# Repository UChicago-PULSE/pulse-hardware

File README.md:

# pulse-hardware
This is the central repository for documents related to PULSE-A hardware development. Each subteam has a folder containing documentation for their specific hardware. 

# Subteam Folders
Subteams are in charge of managing their respective folders in accordance with our teamwide git SOP. Please see the Git SOP document on Notion for more details.

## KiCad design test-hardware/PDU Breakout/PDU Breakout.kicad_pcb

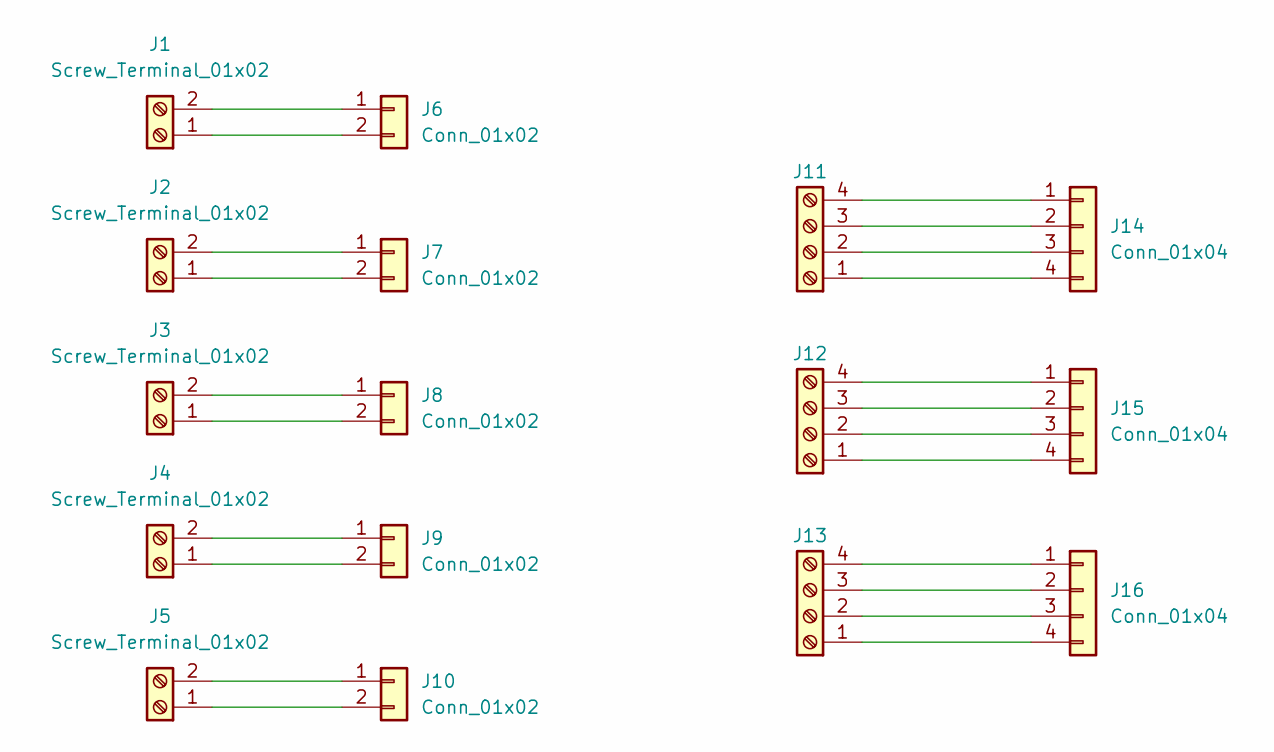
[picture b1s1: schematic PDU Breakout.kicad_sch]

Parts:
J1, J2, J3, J4, J5: Screw_Terminal_01x02; TerminalBlock_Phoenix_PT-1,5-2-3.5-H_1x02_P3.50mm_Horizontal
J6, J7, J8, J9, J10: Conn_01x02; Molex_Pico-Lock_205338-0002_1x02-1MP_P2.00mm_Horizontal
J11, J12, J13: Screw_Terminal_01x04; TerminalBlock_Phoenix_PT-1,5-4-3.5-H_1x04_P3.50mm_Horizontal
J14, J15, J16: Conn_01x04; Molex_Pico-Lock_205338-0004_1x04-1MP_P2.00mm_Horizontal

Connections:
unnamed: J1.1, J6.2
unnamed: J1.2, J6.1
unnamed: J2.1, J7.2
unnamed: J2.2, J7.1
unnamed: J3.1, J8.2
unnamed: J3.2, J8.1
unnamed: J4.1, J9.2
unnamed: J4.2, J9.1
unnamed: J5.2, J10.1
unnamed: J5.1, J10.2
unnamed: J11.1, J14.4
unnamed: J11.2, J14.3
unnamed: J11.3, J14.2
unnamed: J11.4, J14.1
unnamed: J12.1, J15.4
unnamed: J12.2, J15.3
unnamed: J12.3, J15.2
unnamed: J12.4, J15.1
unnamed: J13.1, J16.4
unnamed: J13.2, J16.3
unnamed: J13.3, J16.2
unnamed: J13.4, J16.1

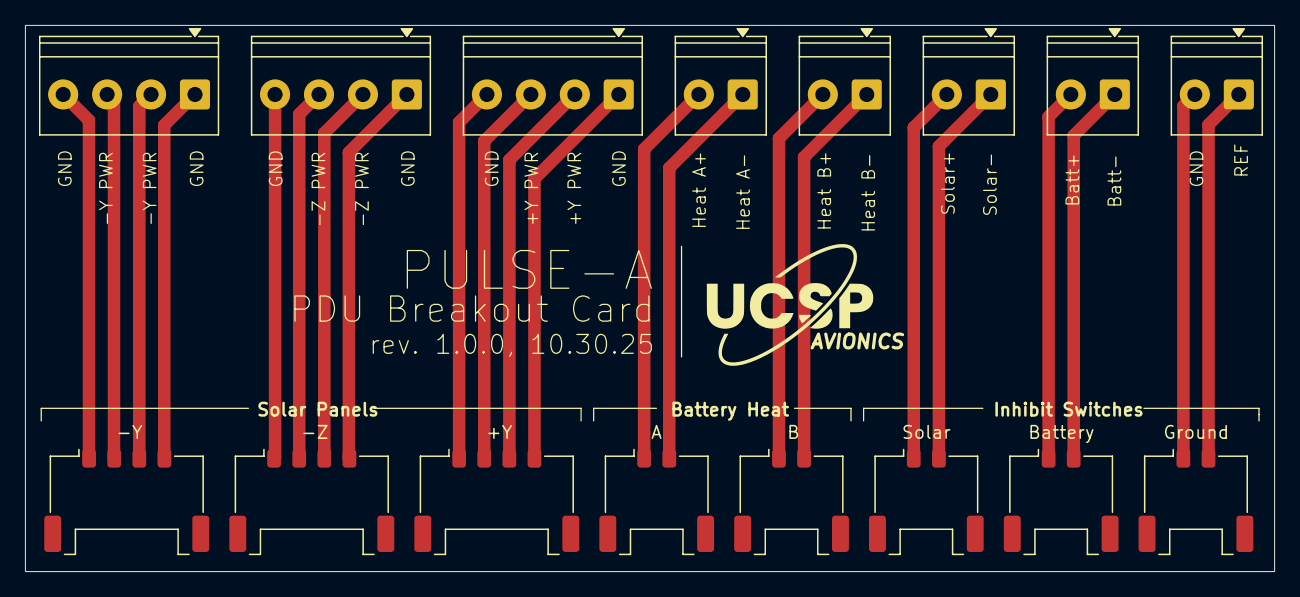
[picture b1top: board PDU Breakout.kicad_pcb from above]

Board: 2 copper layers, 99.5 x 43.5 mm, 16 parts (0 on the bottom side), 22 nets.

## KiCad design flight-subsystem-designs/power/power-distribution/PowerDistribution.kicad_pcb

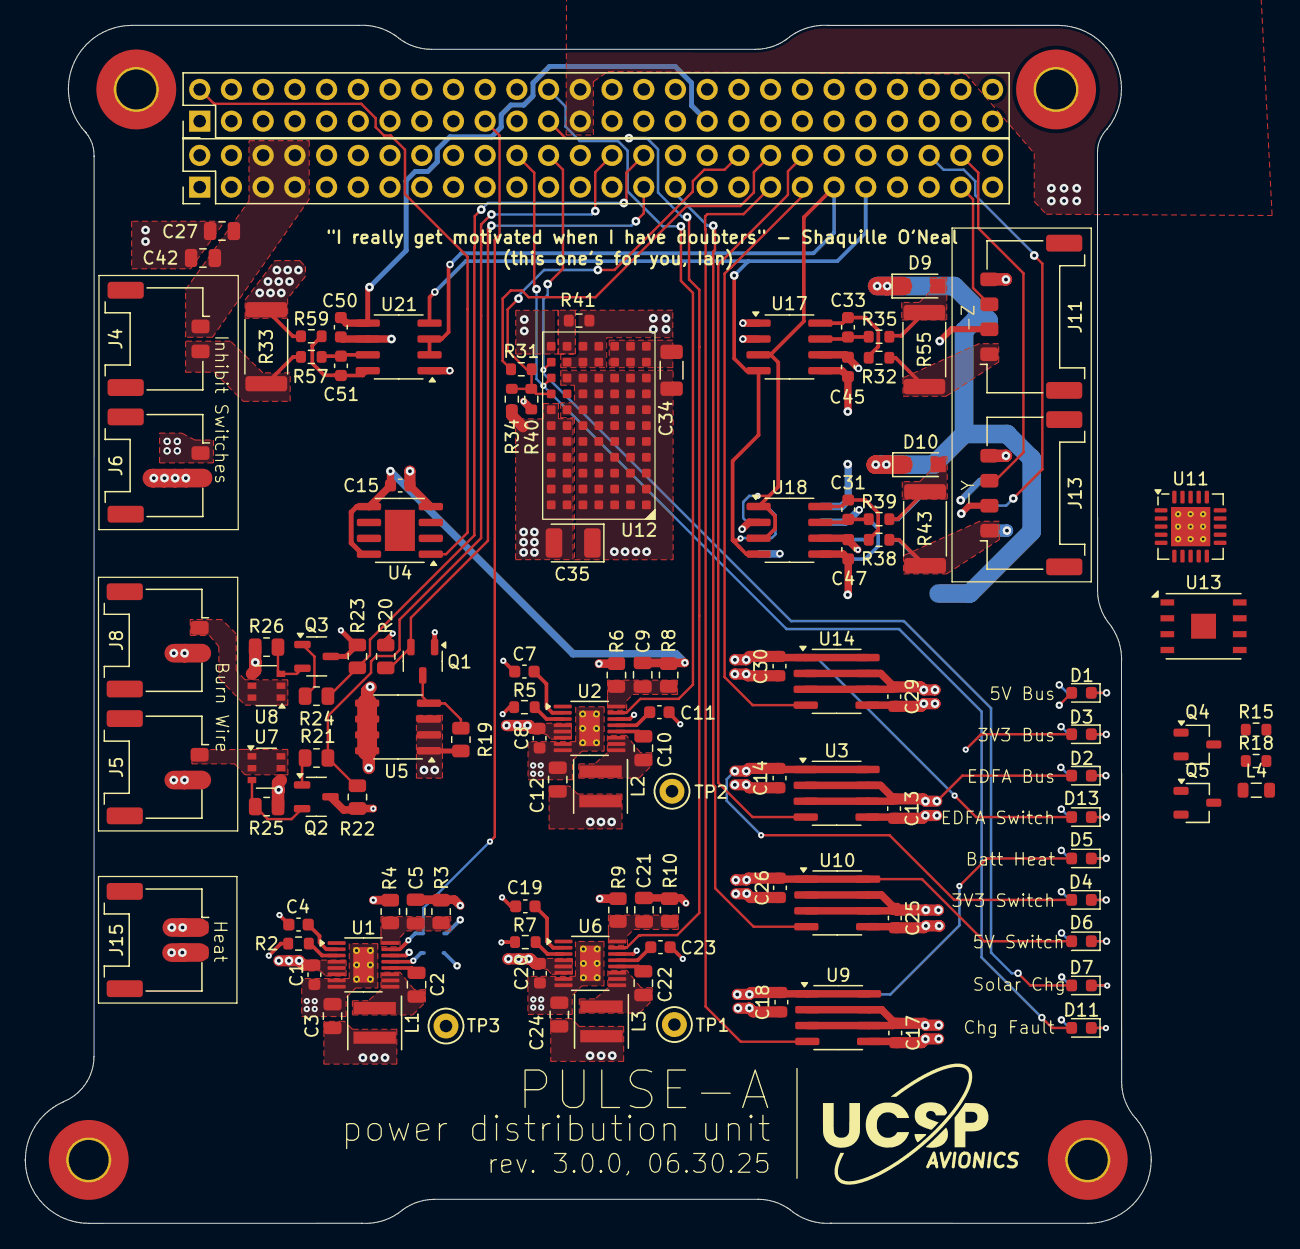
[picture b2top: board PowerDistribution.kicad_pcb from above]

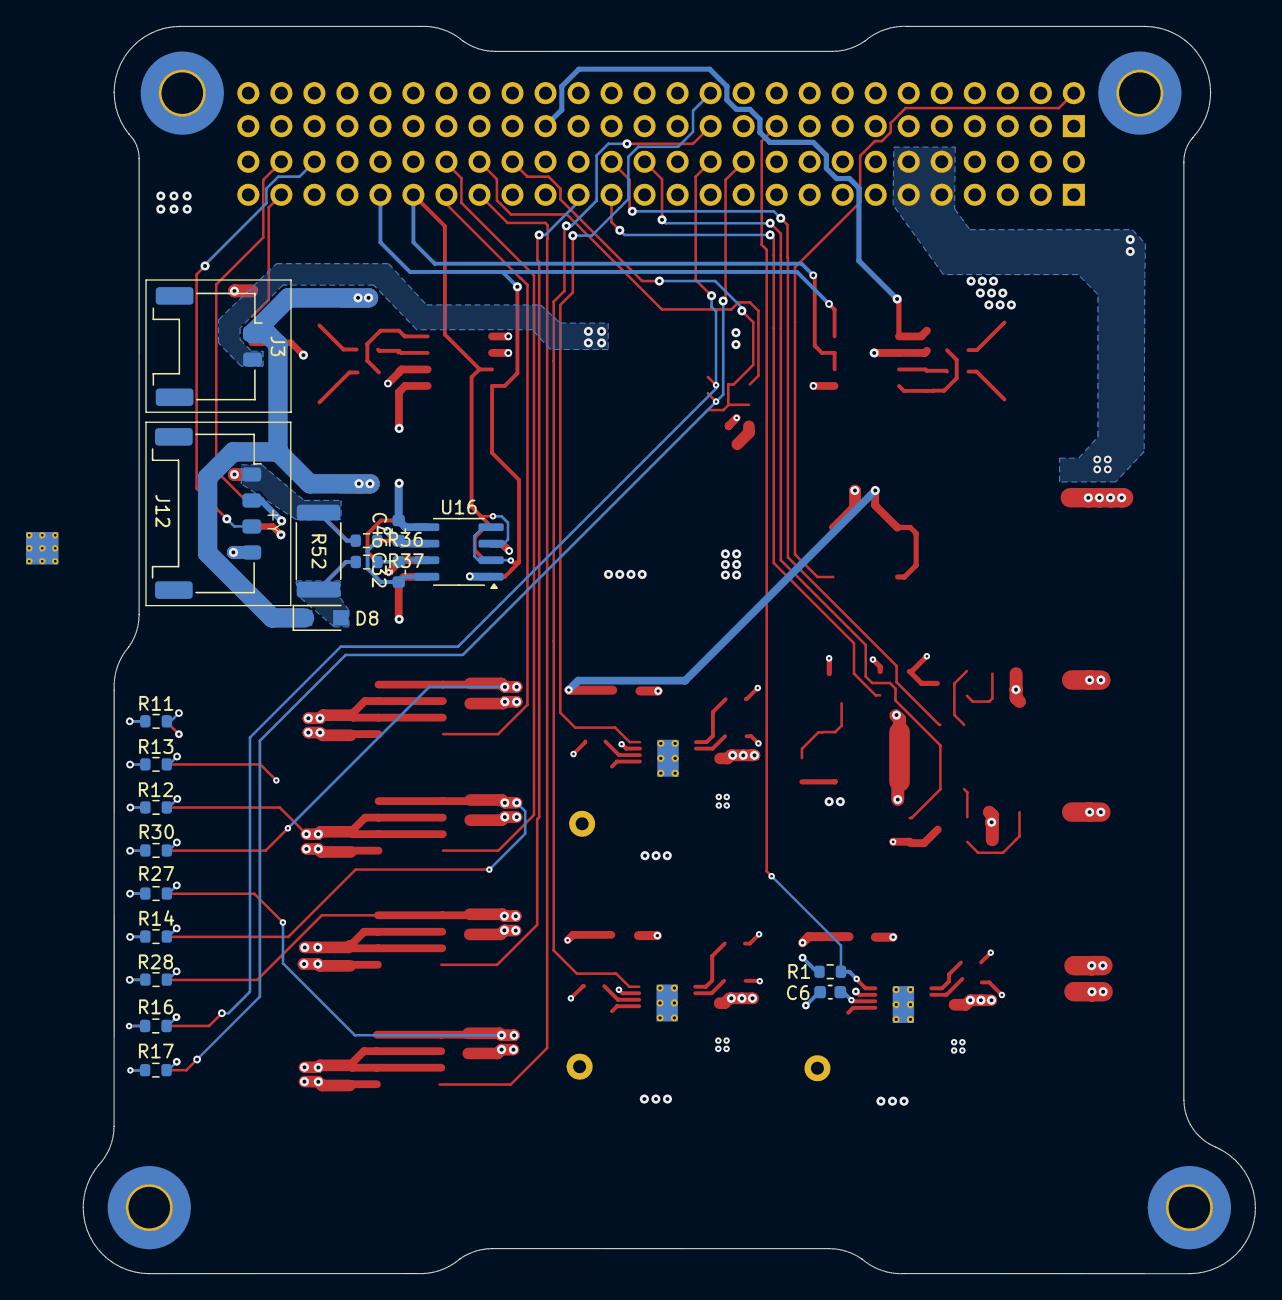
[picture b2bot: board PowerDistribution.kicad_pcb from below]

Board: 4 copper layers, 90.2 x 96.0 mm, 141 parts (20 on the bottom side), 91 nets.

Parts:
C1, C8, C20: 4.7uF; C_0603_1608Metric
C2, C10, C22, C27: 0.1uF; C_0805_2012Metric
C3, C12, C24: 68uF; C_0805_2012Metric
C4, C7, C19: 10nF; C_0603_1608Metric
C5, C21: 10pF; C_0805_2012Metric
C6, C11, C14, C18, C23, C26, C30, C31, C32, C33, C51: 1uF; C_0603_1608Metric
C9: 4.7pF; C_0805_2012Metric
C13, C15, C17, C25, C29: 0.1uF; C_0603_1608Metric
C34: 4.7uF; C_1206_3216Metric
C35: 4.7uF; CP_EIA-3528-12_Kemet-T
C42: 22uF; C_0805_2012Metric
C45, C46, C47, C50: 0.1UF; C_0603_1608Metric
D1, D2, D3, D7, D11: 150060VS75000; LED_0603_1608Metric
D4, D5, D6, D13: 150060AS75000; LED_0603_1608Metric
D8, D9, D10: PMEG10020ELRX; Nexperia_CFP3_SOD-123W
H1, H2, H3, H4: MountingHole; MountingHole_3.2mm_M3_Pad_TopBottom
J1, J2: Conn_02x26_Odd_Even; PinHeader_2x26_P2.54mm_Vertical
J3, J4, J5, J6, J8, J15: Conn_01x02; Molex_Pico-Lock_205338-0002_1x02-1MP_P2.00mm_Horizontal
J11, J12, J13: Conn_01x04; Molex_Pico-Lock_205338-0004_1x04-1MP_P2.00mm_Horizontal
L1, L3: 10uH; L_Coilcraft_XxL4040
L2: 8.2uH; L_Coilcraft_XxL4040
L4: AIMC-0805-2N2S-T; L_0805_2012Metric
Q1: BC848ALT1G; SOT-23-3
Q2, Q3: IRLML2803PBFCT; SOT-23-3
Q4, Q5: NMOS; TSOT-23
R1: 100k; R_0603_1608Metric
R2, R5, R7: 110k; R_0603_1608Metric
R3, R8, R10: 1M; R_0805_2012Metric
R4, R9: 243k; R_0805_2012Metric
R6: 412k; R_0805_2012Metric
R11, R12, R14, R16, R17, R27, R28: 150; R_0603_1608Metric
R13, R30: 65; R_0603_1608Metric
R15, R18: 1M; R_0603_1608Metric
R19, R20, R22, R23: 10k; R_0805_2012Metric
R21, R24: 4.7k; R_0805_2012Metric
R25, R26: 100k; R_0805_2012Metric
R31, R34: 549k; R_0603_1608Metric
R32, R35, R36, R37, R38, R39, R57, R59: 10; R_0603_1608Metric
R33, R43, R52, R55: 2m; R_2512_6332Metric
R40: 459k; R_0603_1608Metric
R41: 0; R_0603_1608Metric
TP1, TP2, TP3: TestPoint_Keystone_5000-5004_Miniature
U1, U2, U6: LT8610; MSOP-16-1EP_3x4.039mm_P0.5mm_EP1.651x2.845mm_ThermalVias
U3, U5, U9, U10, U14: SOIC-8_3.9x4.9mm_P1.27mm
U4: SOIC-8-1EP_3.9x4.9mm_P1.27mm_EP2.41x3.3mm
U7, U8: TSOP-6_1.65x3.05mm_P0.95mm
U11: Texas_RGW0020A_VQFN-20-1EP_5x5mm_P0.65mm_EP3.15x3.15mm_Ther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
U12: LTM8062AIV-PBF; LGA-77
U13: DFN-8-1EP_6x5mm_P1.27mm_EP2x2mm
U16, U17, U18, U21: INA219AxD; SOIC-8_3.9x4.9mm_P1.27mm

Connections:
3V3: C9.2, C12.2, C15.2, C29.1, D3.2 (A), J2.27, J2.28, J11.2, J12.2, J13.2, L2.2, R8.2, TP2.1, U2.14 (BIAS), U4.5 (SHUTDOWN), U4.8 (V_IN), U13.8 (VDD), U14.2 (V_IN1), U14.3 (V_INS), U14.6 (V_IN3), U14.7 (V_IN2)
3V3_S: C30.1, C45.2, C46.2, C47.2, C50.2, D13.2 (A), J1.34, J2.33, U14.1 (V_OUT1), U14.8 (V_OUT2), U16.5 (VS), U17.5 (VS), U18.5 (VS), U21.5 (VS)
3V3_STAT: J2.24, U2.15 (PG)
3V3_S_EN: J1.39, U14.4 (EN)
5V: C17.1, C21.2, C24.2, C25.1, D1.2 (A), J2.25, J2.26, L3.2, R10.2, TP1.1, U6.14 (BIAS), U9.2 (V_IN1), U9.3 (V_INS), U9.6 (V_IN3), U9.7 (V_IN2), U10.2 (V_IN1), U10.3 (V_INS), U10.6 (V_IN3), U10.7 (V_IN2)
5V_S: C26.1, D6.2 (A), J1.45, J1.46, U10.1 (V_OUT1), U10.8 (V_OUT2)
5V_STAT: J2.23, U6.15 (PG)
5V_S_EN: J1.31, U10.4 (EN)
/ADJ: J1.36, R31.2, R34.1, R40.2, U12.H7 (ADJ)
/BATT_CS: J4.2, R33.1, R57.1
/BATT_THERM_R: J1.38, R31.1
/CHARGE_VIN: C34.2, U12.K1 (VIN), U12.K2 (VIN), U12.K3 (VIN), U12.L1 (VIN), U12.L2 (VIN), U12.L3 (VIN)
/CHRG: D7.2 (A), J1.24, U12.K7 (*CHRG)
/CS_SOL1_VIN+: C33.2, R32.1, U17.8 (IN+)
/CS_SOL1_VIN-: C33.1, R35.1, U17.7 (IN-)
/CS_SOL2_VIN+: C32.2, R36.1, U16.8 (IN+)
/CS_SOL2_VIN-: C32.1, R37.1, U16.7 (IN-)
/CS_SOL3_VIN+: C31.2, R38.1, U18.8 (IN+)
/CS_SOL3_VIN-: C31.1, R39.1, U18.7 (IN-)
/FAULT: D11.2 (A), J1.22, U12.J7 (*FAULT)
/FB_1: C5.1, R3.1, R4.2, U1.16 (FB)
/FB_2: C9.1, R6.2, R8.1, U2.16 (FB)
/FB_3: C21.1, R9.2, R10.1, U6.16 (FB)
/PDU_TEMP: J2.2, U4.1 (V_OUT)
/RBF_SW: Q4.2 (G), R15.2
/SOLAR_IN_+Y: J12.1, R36.2, R52.2
/SOLAR_IN_-Y: J13.1, R38.2, R43.2
/SOLAR_IN_-Z: J11.1, R32.2, R55.2
/SOLAR_PRE_MPPT: J3.2, R41.1, U12.K4 (VINA), U12.K5 (VINA), U12.K6 (RUN), U12.L4 (VINA), U12.L5 (VINA)
/SOLAR_TMP_+Y: J1.48, J12.3
/SOLAR_TMP_-Y: J1.50, J13.3
/SOLAR_TMP_-Z: J1.49, J11.3
/SW_1: C2.2, L1.1, U1.9 (SW), U1.10 (SW), U1.11 (SW)
/SW_2: C10.2, L2.1, U2.9 (SW), U2.10 (SW), U2.11 (SW)
/SW_3: C22.2, L3.1, U6.9 (SW), U6.10 (SW), U6.11 (SW)
/VBATT_IN: C27.2, C42.2, J1.5, J1.6, J1.7, J1.8, Q5.1 (D), R18.2
/VBATT_PRE_INH: J4.1, Q5.3 (S)
/VIN_REG: R41.2, U12.L6 (VINREG)
/b1: J5.1, U7.1 (D2), U7.2 (D3), U7.5 (D4), U7.6 (D1)
/b2: J8.1, U8.1 (D2), U8.2 (D3), U8.5 (D4), U8.6 (D1)
/sol_1_diode: D9.2 (A), R35.2, R55.1
/sol_2_diode: D8.2 (A), R37.2, R52.1
/sol_3_diode: D10.2 (A), R39.2, R43.1
BURN_FET: J1.29, Q1.2 (B), R20.1
EDFA_5V: C3.2, C5.2, C13.1, D2.2 (A), L1.2, R1.1, R3.2, TP3.1, U1.14 (BIAS), U3.2 (V_IN1), U3.3 (V_INS), U3.6 (V_IN3), U3.7 (V_IN2)
EDFA_5V_EN: J1.40, U3.4 (EN)
EDFA_5V_S: C14.1, D4.2 (A), J1.42, J1.44, U3.1 (V_OUT1), U3.8 (V_OUT2)
EDFA_5V_STAT: J2.19, R1.2, U1.15 (PG)
ENAB_BURN_1: J1.28, R21.2, R22.1
ENAB_BURN_2: J1.30, R23.1, R24.2
GND: C1.1, C3.1, C4.1, C6.2, C7.1, C8.1, C11.2, C12.1, C13.2, C14.2, C15.1, C17.2, C18.2, C19.1, C20.2, C23.2, C24.1, C25.2, C26.2, C29.2, C30.2, C34.1, C35.1, C45.1, C46.1, C47.1, C50.1, J2.29, J2.30, J2.31, J2.32, J5.2, J6.2, J8.2, J11.4, J12.4, J13.4, J15.2, L4.1, Q1.1 (E), Q2.3 (S), Q3.3 (S), R2.2, R4.1, R5.2, R6.1, R7.2, R9.1, R11.1, R12.1, R13.1, R14.1, R16.1, R17.1, R20.2, R22.2, R23.2, R27.1, R28.1, R30.1, R40.1, U1.7 (GND), U1.8 (GND), U1.17 (GND), U2.7 (GND), U2.8 (GND), U2.17 (GND), U3.5 (GND), U4.4 (GND), U6.7 (GND), U6.8 (GND), U6.17 (GND), U9.5 (GND), U10.5 (GND), U12.A1 (GND), U12.A2 (GND), U12.A3 (GND), U12.A4 (GND), U12.A5 (GND), U12.B1 (GND), U12.B2 (GND), U12.B3 (GND), U12.B4 (GND), U12.B5 (GND), U12.C1 (GND), U12.C2 (GND), U12.C3 (GND), U12.C4 (GND), U12.C5 (GND), U12.D1 (GND), U12.D2 (GND), U12.D3 (GND), U12.D4 (GND), U12.D5 (GND), U12.E1 (GND), U12.E2 (GND), U12.E3 (GND), U12.E4 (GND), U12.E5 (GND), U12.F1 (GND), U12.F2 (GND), U12.F3 (GND), U12.F4 (GND), U12.F5 (GND), U12.G1 (GND), U12.G2 (GND), U12.G3 (GND), U12.G4 (GND), U12.G5 (GND), U12.G6 (GND), U12.H1 (GND), U12.H2 (GND), U12.H3 (GND), U12.H4 (GND), U12.H5 (GND), U12.J1 (GND), U12.J2 (GND), U12.J3 (GND), U12.J4 (GND), U12.J5 (GND), U12.J6 (TMR), U12.L7 (GND), U13.4 (GND), U14.5 (GND), U16.1 (A1), U16.6 (GND), U17.1 (A1), U17.2 (A0), U17.6 (GND), U18.2 (A0), U18.6 (GND), U21.1 (A1), U21.6 (GND)
GND_REF: C27.1, C42.1, J1.9, J1.10, J1.11, J1.12, J6.1
KAPTON_EN: J1.37, U9.4 (EN)
KAPTON_PWR: C18.1, D5.2 (A), J15.1, U9.1 (V_OUT1), U9.8 (V_OUT2)
unnamed: D1.1 (K), R11.2
unnamed: D2.1 (K), R12.2
unnamed: D3.1 (K), R13.2
unnamed: D4.1 (K), R14.2
unnamed: D5.1 (K), R27.2
unnamed: D6.1 (K), R28.2
unnamed: D7.1 (K), R16.2
unnamed: D11.1 (K), R17.2
unnamed: D13.1 (K), R30.2
unnamed: Q1.3 (C), R19.2, U5.4 (G)
unnamed: Q2.2 (D), R25.1, U7.3 (G)
unnamed: Q2.1 (G), R21.1
unnamed: Q3.2 (D), R26.1, U8.3 (G)
unnamed: Q3.1 (G), R24.1
unnamed: Q4.1 (D), Q5.2 (G), R18.1
unnamed: L4.2, Q4.3 (S), R15.1
unnamed: C2.1, U1.12 (BST)
unnamed: C6.1, U1.13 (INTVcc)
unnamed: R2.1, U1.3 (RT)
unnamed: C4.2, U1.2 (TR/SS)
unnamed: C10.1, U2.12 (BST)
unnamed: C11.1, U2.13 (INTVcc)
unnamed: R5.1, U2.3 (RT)
unnamed: C7.2, U2.2 (TR/SS)
unnamed: R25.2, R26.2, U5.5 (D1), U5.6 (D2), U5.7 (D3), U5.8 (D4), U7.4 (S1), U8.4 (S1)
unnamed: C22.1, U6.12 (BST)
unnamed: C23.1, U6.13 (INTVcc)
unnamed: R7.1, U6.3 (RT)
unnamed: C19.2, U6.2 (TR/SS)
unnamed: U11.3 (VOUT), U11.4 (VOUT), U11.5 (VOUT), U11.6 (VOUT)
unnamed: C51.1, R59.2, U21.8 (IN+)
unnamed: C51.2, R57.2, U21.7 (IN-)
SCL: J1.43, U16.2 (A0), U16.4 (SCL), U17.4 (SCL), U18.4 (SCL), U21.4 (SCL)
SDA: J1.41, U16.3 (SDA), U17.3 (SDA), U18.1 (A1), U18.3 (SDA), U21.2 (A0), U21.3 (SDA)
SOLAR_PRE_INH: D8.1 (K), D9.1 (K), D10.1 (K), J3.1
VBATT: C1.2, C8.2, C20.1, C35.2, J2.45, J2.46, J2.48, R19.1, R33.2, R34.2, R59.1, U1.4 (EN/UV), U1.5 (VIN), U1.6 (VIN), U2.4 (EN/UV), U2.5 (VIN), U2.6 (VIN), U5.1 (S1), U5.2 (S2), U5.3 (S3), U6.4 (EN/UV), U6.5 (VIN), U6.6 (VIN), U12.A6 (BAT), U12.A7 (BAT), U12.B6 (BAT), U12.B7 (BAT), U12.C6 (BAT), U12.C7 (BAT), U12.D6 (BAT), U12.D7 (BAT), U12.E6 (BAT), U12.E7 (BAT), U12.F6 (BAT), U12.F7 (BAT), U12.G7 (BIAS)
VS: U11.10 (VS), U11.11 (VS), U11.12 (VS), U11.13 (VS)

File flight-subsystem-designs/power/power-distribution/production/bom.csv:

Designator,Footprint,Quantity,Value,LCSC Part #
"C1, C20, C8",0603,3,4.7uF,
"C10, C2, C22, C27",0805,4,0.1uF,
"C11, C14, C18, C23, C26, C30, C31, C32, C33, C51, C6",0603,11,1uF,
"C12, C3",0805,2,68uF,
"C13, C15, C17, C25, C29, C45, C46, C47, C50",0603,9,0.1uF,
"C19, C4, C7",0603,3,10nF,
"C21, C5",0805,2,10pF,
C24,0805,1,47uF,
C34,1206,1,4.7uF,
C35,CP_EIA-3528-12_Kemet-T,1,4.7uF,
C42,0805,1,22uF,
C9,0805,1,4.7pF,
"D1, D11, D2, D3, D7",0603,5,150060VS75000,
"D10, D8, D9",Nexperia_CFP3_SOD-123W,3,PMEG10020ELRX,
"D13, D4, D5, D6",0603,4,150060AS75000,
"J1, J2",PinHeader_2x26_P2.54mm_Vertical,2,Conn_02x26_Odd_Even,
"J11, J12, J13",Molex_Pico-Lock_205338-0004_1x04-1MP_P2.00mm_Horizontal,3,Conn_01x04,
"J15, J3, J4, J5, J6, J8",Molex_Pico-Lock_205338-0002_1x02-1MP_P2.00mm_Horizontal,6,Conn_01x02,
L1,L_Coilcraft_XxL4040,1,10uH,
L2,L_Coilcraft_XxL4040,1,8.2uH,
L3,L_Coilcraft_XxL4040,1,4.7uH,
Q1,SOT-23-3,1,BC848ALT1G,
"Q2, Q3",SOT-23-3,2,IRLML2803PBFCT,
R1,0603,1,100k,
"R10, R3, R8",0805,3,1M,
"R11, R12, R14, R16, R17, R27, R28",0603,7,150,
"R13, R30",0603,2,65,
"R19, R20, R22, R23",0805,4,10k,
"R2, R7",0603,2,18.2k,
"R21, R24",0805,2,4.7k,
"R25, R26",0805,2,100k,
"R31, R34",0603,2,549k,
"R32, R35, R36, R37, R38, R39, R57, R59",0603,8,10,
"R33, R43, R52, R55",2512,4,2m,
"R4, R9",0805,2,243k,
R40,0603,1,459k,
R41,0603,1,0,
R5,0603,1,110k,
R6,0805,1,412k,
"TP1, TP2, TP3",TestPoint_Keystone_5000-5004_Miniature,3,~,
"U1, U2, U6",MSOP-16-1EP_3x4.039mm_P0.5mm_EP1.651x2.845mm_ThermalVias,3,LT8610,
"U10, U14, U3, U5, U9",SOIC-8_3.9x4.9mm_P1.27mm,5,~,
U12,LGA-77,1,LTM8062AIV-PBF,
"U16, U17, U18, U21",SOIC-8_3.9x4.9mm_P1.27mm,4,INA219AxD,
U4,SOIC-8-1EP_3.9x4.9mm_P1.27mm_EP2.41x3.3mm,1,~,
"U7, U8",TSOP-6_1.65x3.05mm_P0.95mm,2,~,

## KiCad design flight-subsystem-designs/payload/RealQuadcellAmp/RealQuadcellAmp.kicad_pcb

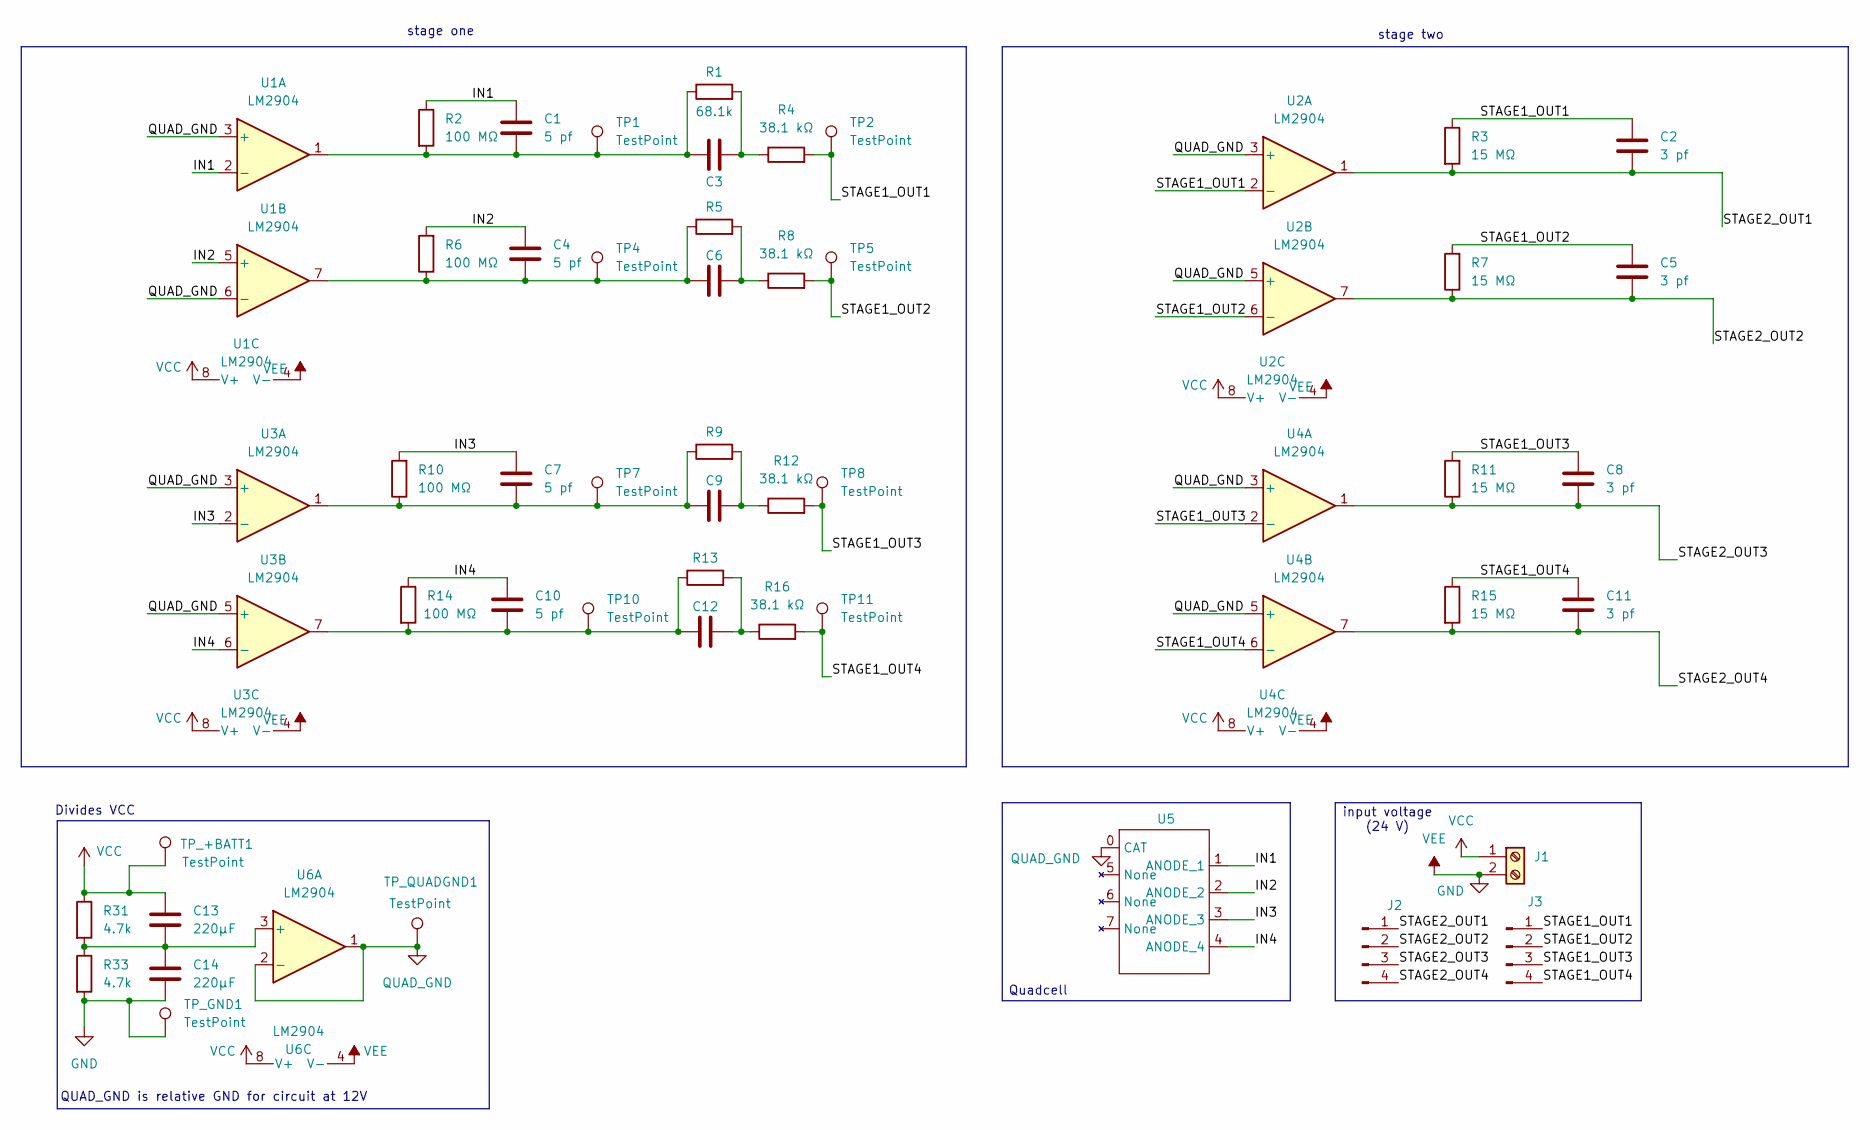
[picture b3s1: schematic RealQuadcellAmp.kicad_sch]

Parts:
C1, C4, C7, C10: 5 pf; C_0805_2012Metric_Pad1.18x1.45mm_HandSolder
C2, C5, C8, C11: 3 pf; C_0805_2012Metric_Pad1.18x1.45mm_HandSolder
C3, C6, C9, C12: 330 pf; C_0805_2012Metric_Pad1.18x1.45mm_HandSolder
C13, C14: 220µF; CP_Radial_D5.0mm_P2.00mm
J1: Screw_Terminal_01x02; TerminalBlock_bornier-2_P5.08mm
J2, J3: Conn_01x04_Pin; PinHeader_1x04_P2.54mm_Vertical
R1: 68.1k; R_0805_2012Metric_Pad1.20x1.40mm_HandSolder
R2, R6, R10, R14: 100 MΩ; R_0805_2012Metric_Pad1.20x1.40mm_HandSolder
R3, R7, R11, R15: 15 MΩ; R_0805_2012Metric_Pad1.20x1.40mm_HandSolder
R4, R8, R12, R16: 38.1 kΩ; R_0805_2012Metric_Pad1.20x1.40mm_HandSolder
R5, R9, R13: 68.1 kΩ; R_0805_2012Metric_Pad1.20x1.40mm_HandSolder
R31, R33: 4.7k; R_0805_2012Metric_Pad1.20x1.40mm_HandSolder
TP1, TP2, TP4, TP5, TP7, TP8, TP10, TP11: TestPoint; TestPoint_Pad_2.0x2.0mm
TP_+BATT1: TestPoint; TestPoint_THTPad_1.0x1.0mm_Drill0.5mm
TP_GND1: TestPoint; TestPoint_THTPad_1.0x1.0mm_Drill0.5mm
TP_QUADGND1: TestPoint; TestPoint_THTPad_1.0x1.0mm_Drill0.5mm
U1, U2, U3, U4, U6: LM2904; SOIC-8_3.9x4.9mm_P1.27mm
U5: InGaAS-Q1000

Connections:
/IN1: C1.1, R2.1, U1.2 (-), U5.1 (ANODE_1)
/IN2: C4.1, R6.2, U1.5 (+), U5.2 (ANODE_2)
/IN3: C7.1, R10.2, U3.2 (-), U5.3 (ANODE_3)
/IN4: C10.1, R14.1, U3.6 (-), U5.4 (ANODE_4)
/STAGE1_OUT1: C2.1, J3.1, R3.1, R4.2, TP2.1, U2.2 (-)
/STAGE1_OUT2: C5.1, J3.2, R7.2, R8.2, TP5.1, U2.6 (-)
/STAGE1_OUT3: C8.1, J3.3, R11.2, R12.2, TP8.1, U4.2 (-)
/STAGE1_OUT4: C11.1, J3.4, R15.1, R16.2, TP11.1, U4.6 (-)
/STAGE2_OUT1: C2.2, J2.1, R3.2, U2.1; also elsewhere on the board
/STAGE2_OUT2: C5.2, J2.2, R7.1, U2.7; also elsewhere on the board
/STAGE2_OUT3: C8.2, J2.3, R11.1, U4.1; also elsewhere on the board
/STAGE2_OUT4: C11.2, J2.4, R15.2, U4.7; also elsewhere on the board
GND: C14.2, J1.2, R33.2, TP_GND1.1, U1.4 (V-), U2.4 (V-), U3.4 (V-), U4.4 (V-), U6.4 (V-)
unnamed: C1.2, C3.1, R1.1, R2.2, TP1.1, U1.1
unnamed: C3.2, R1.2, R4.1
unnamed: C4.2, C6.1, R5.1, R6.1, TP4.1, U1.7
unnamed: C6.2, R5.2, R8.1
unnamed: C7.2, C9.1, R9.1, R10.1, TP7.1, U3.1
unnamed: C9.2, R9.2, R12.1
unnamed: C10.2, C12.1, R13.1, R14.2, TP10.1, U3.7
unnamed: C12.2, R13.2, R16.1
unnamed: C13.2, C14.1, R31.2, R33.1, U6.3 (+)
QUAD_GND: TP_QUADGND1.1, U1.3 (+), U1.6 (-), U2.3 (+), U2.5 (+), U3.3 (+), U3.5 (+), U4.3 (+), U4.5 (+), U5.0 (CAT), U6.1, U6.2 (-)
VCC: C13.1, J1.1, R31.1, TP_+BATT1.1, U1.8 (V+), U2.8 (V+), U3.8 (V+), U4.8 (V+), U6.8 (V+)

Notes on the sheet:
Quadcell
Divides VCC
QUAD_GND is relative GND for circuit at 12V
input voltage (24 V)
stage two
stage one

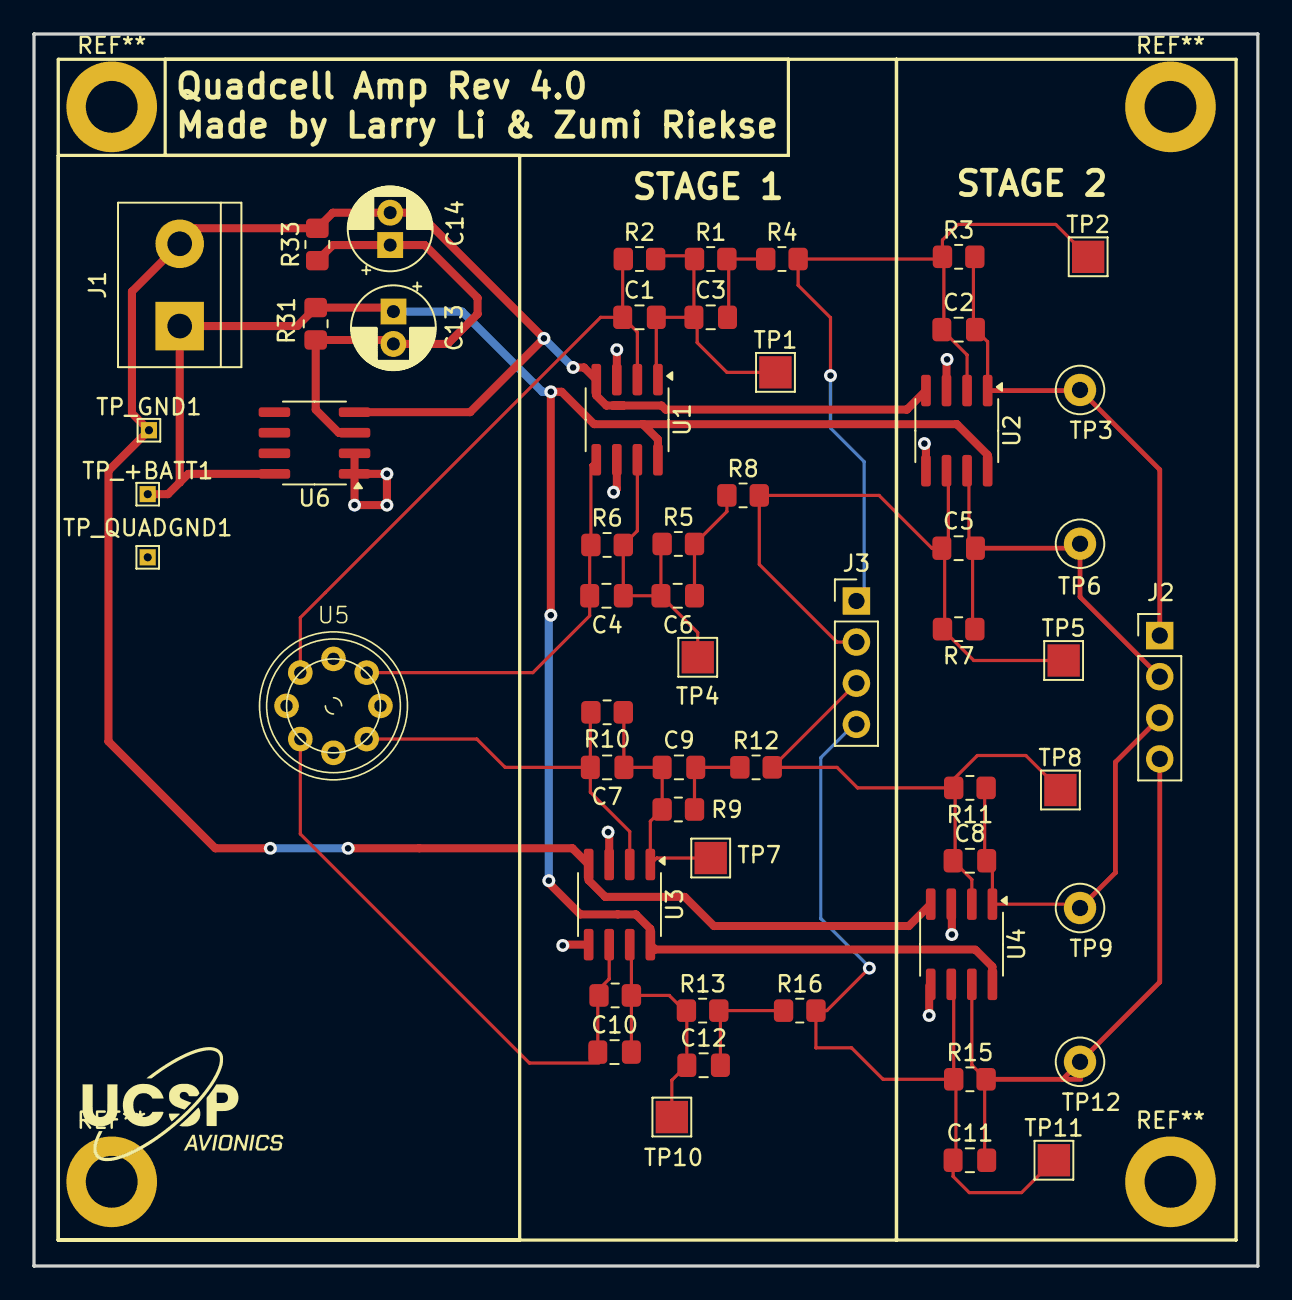
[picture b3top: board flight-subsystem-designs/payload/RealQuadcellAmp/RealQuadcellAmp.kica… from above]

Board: 2 copper layers, 75.6 x 76.1 mm, 56 parts (0 on the bottom side), 24 nets.

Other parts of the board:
TP3, TP6, TP9, TP12: OUTPUT; TestPoint_Loop_D2.50mm_Drill1.0mm

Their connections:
/STAGE2_OUT1: TP3.1; also elsewhere on the board
/STAGE2_OUT2: TP6.1; also elsewhere on the board
/STAGE2_OUT3: TP9.1; also elsewhere on the board
/STAGE2_OUT4: TP12.1; also elsewhere on the board

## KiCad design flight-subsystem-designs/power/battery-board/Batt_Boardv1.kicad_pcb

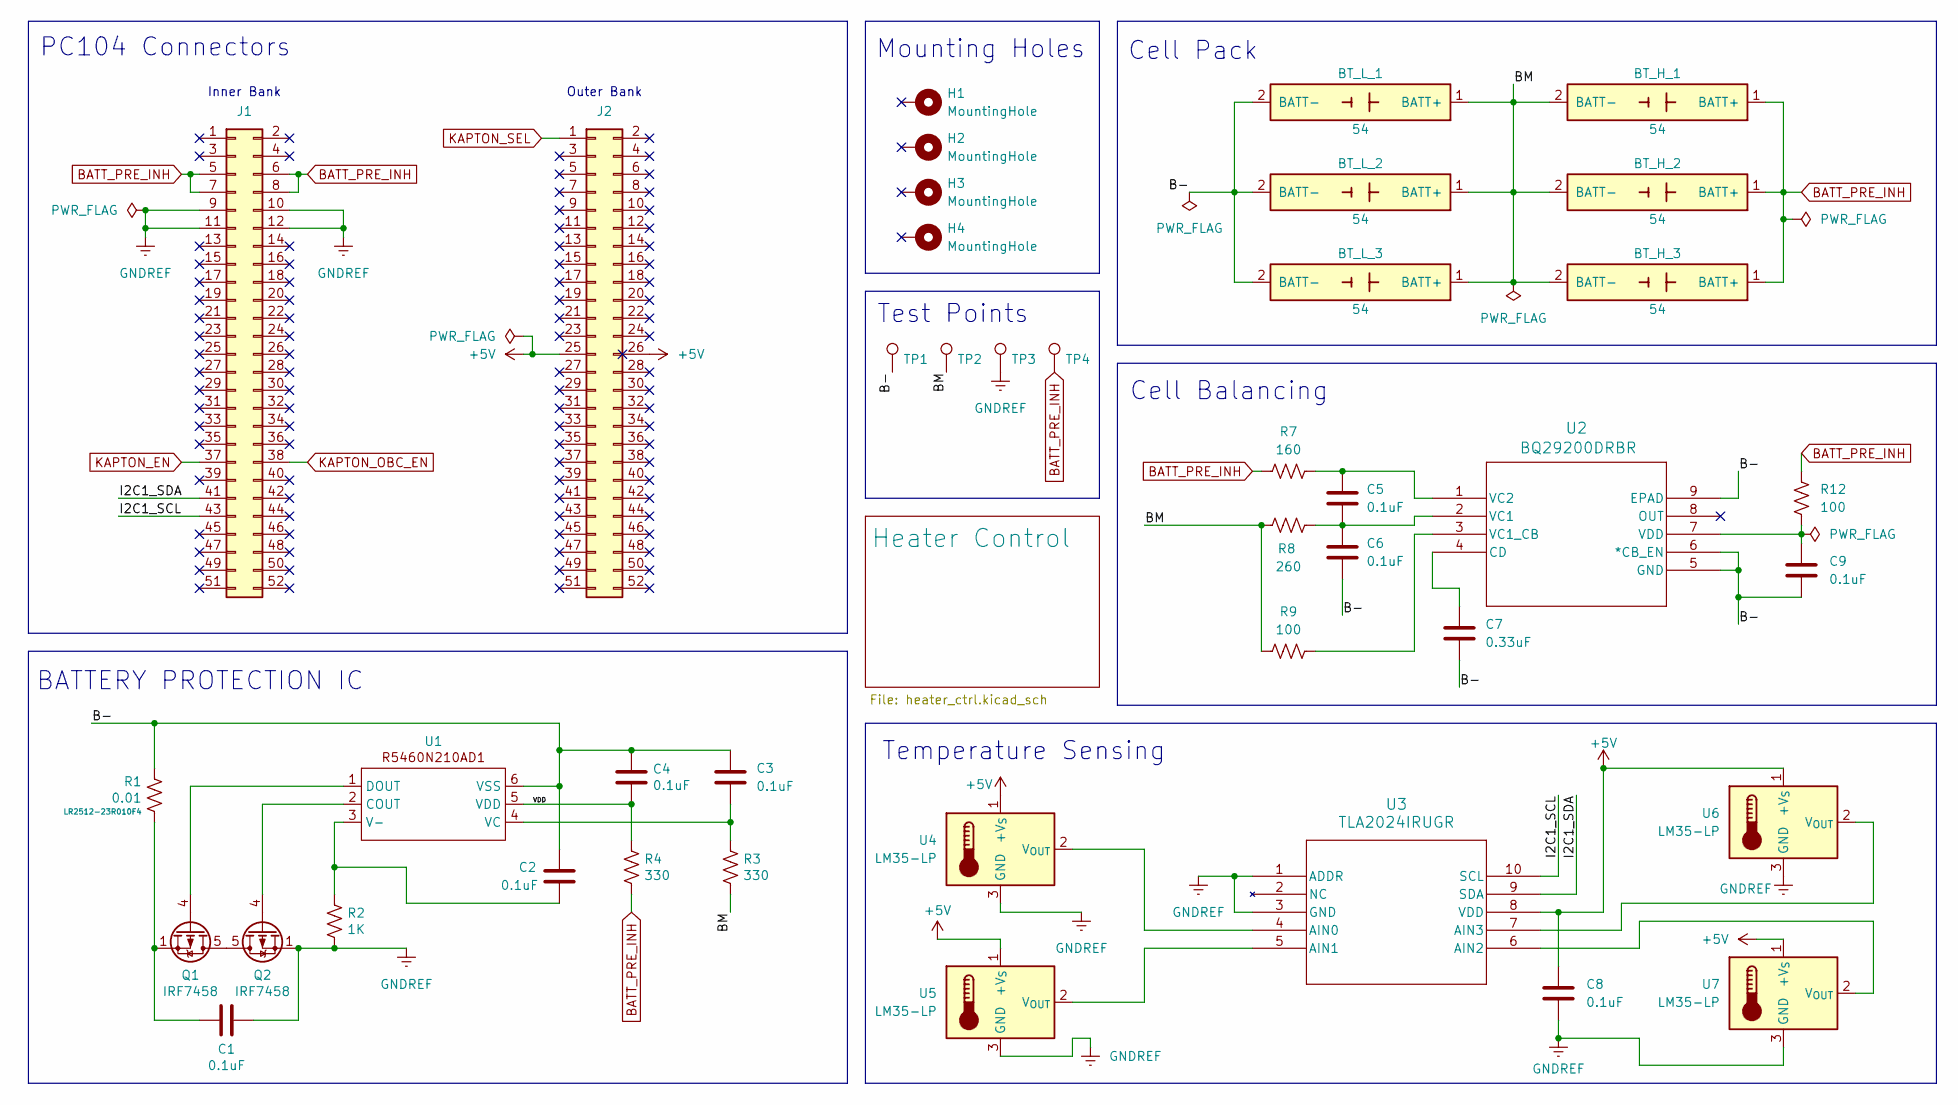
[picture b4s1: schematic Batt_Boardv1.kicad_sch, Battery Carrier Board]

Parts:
BT_H_1, BT_H_2, BT_H_3: 54; BAT_254_1; PARTREV E
BT_L_1, BT_L_2, BT_L_3: 54; BAT_254_1; PARTREV E
C1, C2, C3, C4, C5, C6, C8, C9: 0.1uF; C_0805_2012Metric
C7: 0.33uF; C_0805_2012Metric
H1, H2, H3, H4: MountingHole; MountingHole_3.2mm_M3_Pad_TopBottom
J1, J2: Conn_02x26_Odd_Even; PinHeader_2x26_P2.54mm_Vertical
Q1, Q2: IRF7458; SOIC-8_3.9x4.9mm_P1.27mm
R1: 0.01; R_2512_6332Metric
R2: 1K; R_0603_1608Metric
R3, R4: 330; R_0603_1608Metric
R7: 160; R_0805_2012Metric
R8: 260; R_0805_2012Metric
R9, R12: 100; R_0805_2012Metric
TP1, TP2, TP3, TP4: TestPoint; TestPoint_Loop_D1.80mm_Drill1.0mm_Beaded
U1: R5460N210AD1; SOT-23-6
U2: BQ29200DRBR; DRB8_1P6X2P4
U3: TLA2024IRUGR; RUG10_TEX
U4, U5, U6, U7: LM35-LP; TO-92_Inline

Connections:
+5V: C8.1, J2.25, J2.26, U3.8 (VDD), U4.1 (+V_{S}), U5.1 (+V_{S}), U6.1 (+V_{S}), U7.1 (+V_{S})
/B-: BT_L_1.2 (BATT-), BT_L_2.2 (BATT-), BT_L_3.2 (BATT-), C2.1, C3.1, C4.1, C6.2, C7.2, C9.2, R1.1, TP1.1, U1.6 (VSS), U2.5 (GND), U2.6 (*CB_EN), U2.9 (EPAD)
/BM: BT_H_1.2 (BATT-), BT_H_2.2 (BATT-), BT_H_3.2 (BATT-), BT_L_1.1 (BATT+), BT_L_2.1 (BATT+), BT_L_3.1 (BATT+), R3.1, R8.1, R9.1, TP2.1
/I2C1_SCL: J1.43, U3.10 (SCL)
/I2C1_SDA: J1.41, U3.9 (SDA)
/VDD: C4.2, R4.2, U1.5 (VDD)
BATT_PRE_INH: BT_H_1.1 (BATT+), BT_H_2.1 (BATT+), BT_H_3.1 (BATT+), J1.5, J1.6, J1.7, J1.8, R4.1, R7.1, R12.1, TP4.1; also elsewhere on the board
GNDREF: C1.2, C8.2, J1.9, J1.10, J1.11, J1.12, Q2.1 (S), Q2.2 (S), Q2.3 (S), R2.2, TP3.1, U3.1 (ADDR), U3.3 (GND), U4.3 (GND), U5.3 (GND), U6.3 (GND), U7.3 (GND); also elsewhere on the board
KAPTON_EN: J1.37; also elsewhere on the board
KAPTON_OBC_EN: J1.38; also elsewhere on the board
KAPTON_SEL: J1.36; also elsewhere on the board
unnamed: C1.1, Q1.1 (S), Q1.2 (S), Q1.3 (S), R1.2
unnamed: Q1.5 (D), Q1.6 (D), Q1.7 (D), Q1.8 (D), Q2.5 (D), Q2.6 (D), Q2.7 (D), Q2.8 (D)
unnamed: Q1.4 (G), U1.1 (DOUT)
unnamed: Q2.4 (G), U1.2 (COUT)
unnamed: C2.2, R2.1, U1.3 (V-)
unnamed: C3.2, R3.2, U1.4 (VC)
unnamed: C7.1, U2.4 (CD)
unnamed: C5.2, C6.1, R8.2, U2.2 (VC1)
unnamed: R9.2, U2.3 (VC1_CB)
unnamed: C5.1, R7.2, U2.1 (VC2)
unnamed: C9.1, R12.2, U2.7 (VDD)
unnamed: U3.4 (AIN0), U4.2 (V_{OUT})
unnamed: U3.5 (AIN1), U5.2 (V_{OUT})
unnamed: U3.6 (AIN2), U7.2 (V_{OUT})
unnamed: U3.7 (AIN3), U6.2 (V_{OUT})

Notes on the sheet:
Cell Balancing
Test Points
Cell Pack
Outer Bank
Inner Bank
Mounting Holes
BATTERY PROTECTION IC
Temperature Sensing
PC104 Connectors
